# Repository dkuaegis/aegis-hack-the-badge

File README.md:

# Hack The Badge Ver.3

## Sponsored by

<p align="center">
  
  &nbsp;&nbsp;&nbsp;&nbsp;
  
</p>

해당 프로젝트는 EasyEDA로 제작되었고 EasyEDA 측의 제작 지원을 받았습니다. <br>
PCB 제작은 JLCPCB 측의 지원을 받았습니다.

## 프로젝트 소개

`Hack The Badge Ver.3`는 정보보안 동아리 Aegis가 MSG CTF 본선
부스에서 운영하는 체험형 하드웨어 해킹 프로젝트입니다. ESP32-S3를
기반으로 OLED, 버튼, LED, USB Serial, UART, challenge pad, 부저를
하나의 PCB 배지에 구성해, 행사 배지와 해킹 문제 도구로 함께 사용할
수 있도록 제작했습니다.

## 제작 목적

참가자가 일반적인 소프트웨어 CTF를 넘어 실제 PCB의 입출력 장치와
통신 인터페이스를 직접 살펴보며 하드웨어 보안을 체험하도록 하는 것이
목표입니다. 문제 풀이 결과가 화면, LED, 소리로 즉시 반영되는 상호작용을
통해 하드웨어 해킹을 처음 접하는 참가자도 쉽게 몰입할 수 있도록
구성했습니다.

## 체험 활동

참가자는 배지를 USB로 연결한 뒤 다음 활동을 진행합니다.

- Serial 터미널에서 문제를 확인하고 FLAG를 제출합니다.
- OLED와 버튼으로 문제, 힌트, 미니게임을 이용합니다.
- UART와 challenge pad를 분석해 숨겨진 하드웨어 문제를 해결합니다.
- OLED, LED, 부저를 통해 문제 진행 상태와 완료 결과를 확인합니다.

## 현재 제작 리비전

- 리비전: Hack The Badge Ver.3
- MCU: ESP32-S3-WROOM-1-N8R8
- 디스플레이: HS96L03W2C03 0.96 inch I2C OLED, PCBA 이후 수작업 납땜
- 사용자 I/O: USB Serial, 3.3 V UART, 버튼 3개, 상태 LED 5개
- Challenge I/O: 1 kOhm 직렬 저항으로 보호되는 `C0`, `C1`, `C2` GPIO pad
- 관리자/디버그: 복구와 bring-up을 위한 후면 staff test pad
- 오디오: MOSFET으로 구동하는 passive buzzer
- PCB 스타일: 검정 solder mask, 흰색 silkscreen, Aegis 방패 외형

## 저장소 구조

```text
assets/brand/                         Aegis, MSG CTF, EasyEDA, JLCPCB 로고
docs/rev3/                            설계, 제작, 스폰서 관련 문서
hardware/design/rev3/kicad/           KiCad 호환 회로도, PCB, 라이브러리
hardware/design/rev3/reference/       BOM 메모, 데이터시트, 전기적 설계 메모
hardware/releases/rev3/jlcpcb/upload/ JLCPCB 업로드용 Gerber, BOM, CPL
hardware/releases/rev3/easyeda-pro/   EasyEDA Pro 프로젝트 패키지와 체크리스트
hardware/releases/rev3/jlcpcb/        제작 파일, 조립 파일, preview, 검증 리포트
archive/                              이전 설계/제작 이력
tools/                                문서 생성 보조 스크립트
firmware/                             ESP32-S3 문제/UI/관리자 펌웨어
admin/                                Python BLE 브리지와 로컬 웹 대시보드
player-console/                       플레이어용 Web Serial 콘솔과 Docker 배포 구성
```

펌웨어 빌드, 문제 교체, Serial 명령과 무선 관리자 사용법은
[`firmware/README.md`](firmware/README.md)를 참고하세요.
브리지 설치, OS별 실행법과 운영 안내는
[`admin/README.md`](admin/README.md)를 참고하세요.
플레이어용 브라우저 USB 콘솔의 Docker 실행과 HTTPS 배포 안내는
[`player-console/README.md`](player-console/README.md)를 참고하세요.

## 펌웨어 빠른 시작

먼저 루트의 `.env.example`을 `.env`로 복사하고 `BADGE_ADMIN_KEY`와
`BADGE_FINAL_FLAG`를 비공개로 설정하세요. 펌웨어 빌드와 관리자 브리지가 같은
파일을 읽습니다. `.env`와 펌웨어 바이너리는 공개하거나 Git에 추가하지 마세요.

펌웨어 대상은 `ESP32-S3-WROOM-1-N8R8`이며 PlatformIO 환경 이름은
`esp32-s3-rev3`입니다. 데이터 통신이 가능한 USB-C 케이블로 배지를 연결한
뒤 저장소 루트에서 다음 명령을 실행합니다.

```bash
cd firmware
pio run
pio device list
pio run -t upload
pio device monitor
```

`pio run`은 첫 실행 시 ESP32 플랫폼, Arduino framework와 U8g2 의존성을
자동으로 내려받아 빌드합니다. Serial monitor 속도는 `platformio.ini`에
`115200`으로 설정되어 있습니다. 포트 자동 선택이 실패하면 OS에서 확인한
포트를 직접 지정합니다.

```bash
# Windows 예시
pio run -t upload --upload-port COM5
pio device monitor --port COM5

# macOS 예시
pio run -t upload --upload-port /dev/cu.usbmodemXXXX
pio device monitor --port /dev/cu.usbmodemXXXX

# Linux 예시
pio run -t upload --upload-port /dev/ttyACM0
pio device monitor --port /dev/ttyACM0
```

업로드 포트가 나타나지 않으면 USB 케이블이 충전 전용인지 먼저 확인하고,
`BOOT` 버튼을 누른 상태에서 `EN`을 눌렀다 놓은 뒤 `BOOT`를 놓아 ROM 다운로드
모드로 진입한 다음 다시 업로드합니다. 일반 업로드는 NVS를 지우지 않으므로
기존 풀이 상태와 관리자 페이지에서 편집한 문제는 유지됩니다.

PlatformIO 설치, 완전 초기화, BOOT 복구, 업로드 후 점검, 핀 매핑과 보안
주의사항은 [`firmware/README.md`](firmware/README.md)의 상세 절차를
참고하세요.

## 소프트웨어 구조

참가자 USB Serial과 관리자 BLE 셸은 각자의 입력 상태를 따로 유지합니다.
관리자 PC에서는 하나의 Python 프로세스가 BLE Central, HTTP API,
정적 대시보드를 모두 제공합니다. 인터넷과 공유기는 필요하지 않고,
브라우저는 관리자 PC의 `127.0.0.1` 주소로만 접속합니다.

| 코드 | 역할 |
| --- | --- |
| `firmware/src/main.cpp` | 메인 루프, OLED UI, 버튼·LED, USB/BLE 셸, 미니게임, challenge pad 처리 |
| `firmware/src/problems.h` | 1~4번 기본 문제, 문제 크기 제한, 미니게임 보상 문구 |
| `firmware/src/pins.h` | Rev.3 PCB의 GPIO 매핑 |
| `firmware/src/logic.h` | 상태 비트와 challenge pad 판정 로직 |
| `admin/bridge.py` | 배지 탐색·인증·연결, HTTP API, 대시보드 서빙 |
| `admin/dashboard/index.html` | 배지별 상태, 관리자 셸, 리셋·재부팅·문제 편집 UI |
| `admin/start.py` | 가상환경 생성, pip 의존성 확인·설치, 자가 검사, 서버 실행 |
| `player-console/` | 관리자 기능 없이 브라우저와 USB CDC를 직접 연결하는 정적 웹 콘솔 |

## 참가자 사용 설명서

1. 배지를 USB로 PC에 연결하고 Serial 터미널을 `115200 baud`로 엽니다.
2. `aegis`를 입력한 뒤 `1`~`4`로 문제를 선택합니다.
3. 한국어 문제 본문은 Serial에서, 영문 ASCII 힌트는 OLED에서 확인합니다.
4. 문제 안내에 따라 문제 내부 명령 또는 FLAG를 Serial에 입력합니다.
5. 해결한 문제는 상태 LED와 OLED `STATUS`에 반영됩니다.

Serial 명령:

| 명령 | 기능 |
| --- | --- |
| `1`~`4` | 문제 선택 |
| `hint` | 선택한 문제의 OLED 보기/예시 재표시 |
| `exit` | 현재 문제 나가기 |
| `status` | 문제 풀이 상태 표시 |
| `help` | 사용 가능한 명령 표시 |
| `clear` | Serial 터미널 화면 정리 |
| `aegis` | 시작 배너 재표시 |

OLED 하단의 `LEFT`, `OK`, `RIGHT` 버튼으로 메뉴 이동과 Flappy Hacker를
조작합니다. 미니게임에서 목표 점수를 넘기면 OLED에 추가 힌트가
표시됩니다.

## 관리자 사용 설명서

Python 3.10 이상과 Bluetooth LE가 가능한 PC에서 해당 OS의 스크립트를
실행합니다. 첫 실행 시 `admin/.venv`를 만들고 필요한 pip 패키지를
자동 설치한 뒤 브리지를 시작합니다. 운영 키는 환경변수 또는
`--admin-key '32바이트 이상의 키'`로 전달할 수 있으며, 공개 개발 키는
명령에 `--allow-dev-key`를 붙인 로컬 테스트에서만 허용됩니다.

```bash
# macOS
./admin/start-macos.sh --admin-key 'AEGIS_DEV_ONLY_CHANGE_ME'

# Linux
./admin/start-linux.sh --admin-key 'AEGIS_DEV_ONLY_CHANGE_ME'
```

Windows에서는 터미널에서 `admin\start-windows.bat`을 실행하거나 파일을
더블 클릭합니다. 시작 후 브라우저에서 `http://127.0.0.1:8080`을 엽니다.

대시보드에서 배지를 선택하면 다음 작업을 수행할 수 있습니다.

- 1~4번과 Hidden Access의 풀이 상태 확인
- 개별 또는 현재 연결된 전체 배지의 풀이 상태 초기화·재부팅
- USB 사용자 셸 기능을 포함한 BLE 관리자 셸 사용
- 1~4번 문제의 FLAG/최대 4지선다 유형 개별·일괄 수정

행사 전에는 펌웨어와 브리지의 `BADGE_ADMIN_KEY`를 동일한 운영용
키로 교체하세요. 자세한 OS별 준비, 설정, 문제 편집 제한과 문제 해결은
[`admin/README.md`](admin/README.md)에 정리했습니다.

## 제작 산출물

JLCPCB 업로드 파일:

| 단계     | 파일                                                                       |
| -------- | -------------------------------------------------------------------------- |
| PCB 제작 | `hardware/releases/rev3/jlcpcb/upload/hacking_badge_v3_jlcpcb_gerbers.zip` |
| PCBA BOM | `hardware/releases/rev3/jlcpcb/upload/hacking_badge_v3_jlcpcb_bom.csv`     |
| PCBA CPL | `hardware/releases/rev3/jlcpcb/upload/hacking_badge_v3_jlcpcb_cpl.csv`     |

EasyEDA Pro 프로젝트 패키지:

| 용도                             | 파일                                                                                            |
| -------------------------------- | ----------------------------------------------------------------------------------------------- |
| EasyEDA Pro 실크 호환 프로젝트   | `hardware/releases/rev3/easyeda-pro/upload/hacking_badge_v3_easyeda_pro_silk_compat_import.zip` |
| EasyEDA Pro 프로젝트(KiCad 호환) | `hardware/releases/rev3/easyeda-pro/upload/hacking_badge_v3_easyeda_pro_kicad_import.zip`       |
| EasyEDA Pro 프로젝트 아카이브    | `hardware/releases/rev3/easyeda-pro/reference/ProPrj_hack_the_badge_rev.3.epro2`                |

## 3D Preview

홍보물 제작이나 웹/Blender preview에는 검정 PCB 색상이 보정된 GLB 파일을
사용하는 것을 권장합니다.

| 용도                    | 파일                                                                                |
| ----------------------- | ----------------------------------------------------------------------------------- |
| 검정 PCB 홍보용 GLB     | `hardware/releases/rev3/jlcpcb/preview/3d/hacking_badge_v3_full_assembly_black.glb` |
| 검정 PCB 3D export 묶음 | `hardware/releases/rev3/jlcpcb/preview/3d/hacking_badge_v3_3d_exports_black.zip`    |
| 전체 3D export 묶음     | `hardware/releases/rev3/jlcpcb/preview/3d/hacking_badge_v3_3d_exports.zip`          |

## 검증 상태

현재 확인된 상태:

- Schematic ERC: 0 errors, 0 warnings
- Schematic-to-PCB validation: PASS
- JLCPCB manufacturing validation: PASS
- Gerber ZIP SHA256:
  `b55b42de45568e995e8cb47bb18cfc09abd5469c50e1fb60852d323a703e96b1`

유용한 검증 명령:

```bash
/Applications/KiCad/KiCad.app/Contents/MacOS/kicad-cli sch erc \
  --format report \
  -o hardware/design/rev3/kicad/reports/erc-final.rpt \
  hardware/design/rev3/kicad/hacking_box_v2.kicad_sch

/Applications/KiCad/KiCad.app/Contents/Frameworks/Python.framework/Versions/3.9/bin/python3.9 \
  hardware/design/rev3/kicad/scripts/validate_schematic_against_pcb.py

/Applications/KiCad/KiCad.app/Contents/Frameworks/Python.framework/Versions/3.9/bin/python3.9 \
  hardware/design/rev3/kicad/scripts/validate_manufacturing.py
```

## 참고 사항

- KiCad 파일명은 초기 프로젝트/라이브러리 이름을 유지하기 위해
  `hacking_box_v2`를 사용합니다. 실제 제작 리비전은 Ver.3입니다.
- `OLED1`은 JLCPCB BOM/CPL에서 제외되어 있으며, 별도 구매 후 수작업으로
  납땜하는 기준입니다.
- JLCPCB SMT viewer에서 자동 placement alignment 알림이 뜨면 취소하고,
  기존 CPL 기준 배치가 유지되는지 확인합니다. 방패 형태의 custom outline
  때문에 false offset warning이 뜰 수 있습니다.
- Challenge pad는 3.3 V GPIO 전용입니다. 회로를 의도적으로 수정하지 않은
  상태에서 `VBUS`, `3V3`, `EN`, `BOOT` 단락을 문제 풀이 요소로 노출하지
  마세요.

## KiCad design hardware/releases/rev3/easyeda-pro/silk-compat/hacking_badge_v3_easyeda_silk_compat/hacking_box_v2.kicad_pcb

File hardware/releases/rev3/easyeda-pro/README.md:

# Hacking Badge Ver.3 EasyEDA Pro Package

This directory contains the EasyEDA Pro preparation package for sponsor/coupon
workflow.

## Upload / Import Files

| Purpose | File |
| --- | --- |
| Recommended EasyEDA Pro import package | `upload/hacking_badge_v3_easyeda_pro_silk_compat_import.zip` |
| Raw KiCad source import package | `upload/hacking_badge_v3_easyeda_pro_kicad_import.zip` |
| Previous EasyEDA Pro archive reference | `reference/ProPrj_hack_the_badge_rev.3.epro2` |

Use the silkscreen-compatible import package first when the goal is sponsor
review or coupon use in EasyEDA Pro. It is derived from the current production
KiCad design, but converts filled silkscreen polygons into dense line artwork
because EasyEDA Pro's KiCad importer can otherwise show complex filled logos as
hollow outlines. The raw KiCad import package is kept only as a reference for
format comparison. The `.epro2` file is kept as a reference/native archive
candidate, but it was generated before the final KiCad release checks and must
not be assumed to be identical without review.

## Import Procedure

1. Open EasyEDA Pro.
2. Use the start page import flow for KiCad files, or use the EasyEDA Pro Format
   Converter if direct import fails.
3. Select `upload/hacking_badge_v3_easyeda_pro_silk_compat_import.zip`.
4. After import, open both schematic and PCB.
5. Rebuild/refill copper zones only if EasyEDA Pro asks for it, then compare
   against the KiCad release previews and Gerbers.
6. Run EasyEDA Pro DRC/ERC before using any generated manufacturing output.

## Required Post-Import Checks

- Board outline remains the Aegis shield shape, approximately 84.05 x 100.05 mm.
- USB-C connector sits on the bottom edge with the intentional edge overhang.
- ESP32-S3 antenna keep-out is still clear.
- Front silkscreen includes `Aegis X MSG CTF`, `HACK THE BADGE Ver.3`,
  `Developed By @Z3r0c0k3_`, full Aegis logo, and sponsor mark.
- Rear silkscreen preserves the filled Aegis silhouette and MSG CTF negative
  mark.
- Filled logo areas may look lightly striped at extreme zoom because the
  EasyEDA-compatible package uses dense silkscreen lines instead of KiCad
  filled polygons.
- `C0`, `C1`, `C2` challenge pads route through 1 kOhm series resistors to
  ESP32-S3 GPIO6, GPIO7, GPIO8.
- OLED pin order remains `GND, VCC, SCL, SDA`.
- J1, U1, U2, D1, Q_BZ, LEDs, buzzer diode, and switches have correct rotation.
- Copper zones and clearances match the KiCad/JLCPCB manufacturing release.

## Important Warning

The routed KiCad project and the JLCPCB release package remain the production
source of truth until the EasyEDA Pro import is manually reviewed. EasyEDA Pro
can import KiCad files, but format conversion can change copper-zone results.
Do not manufacture from newly generated EasyEDA Pro Gerbers until visual review,
DRC/ERC, and pin/net checks pass.

## Checksums

See `SHA256SUMS.txt`.

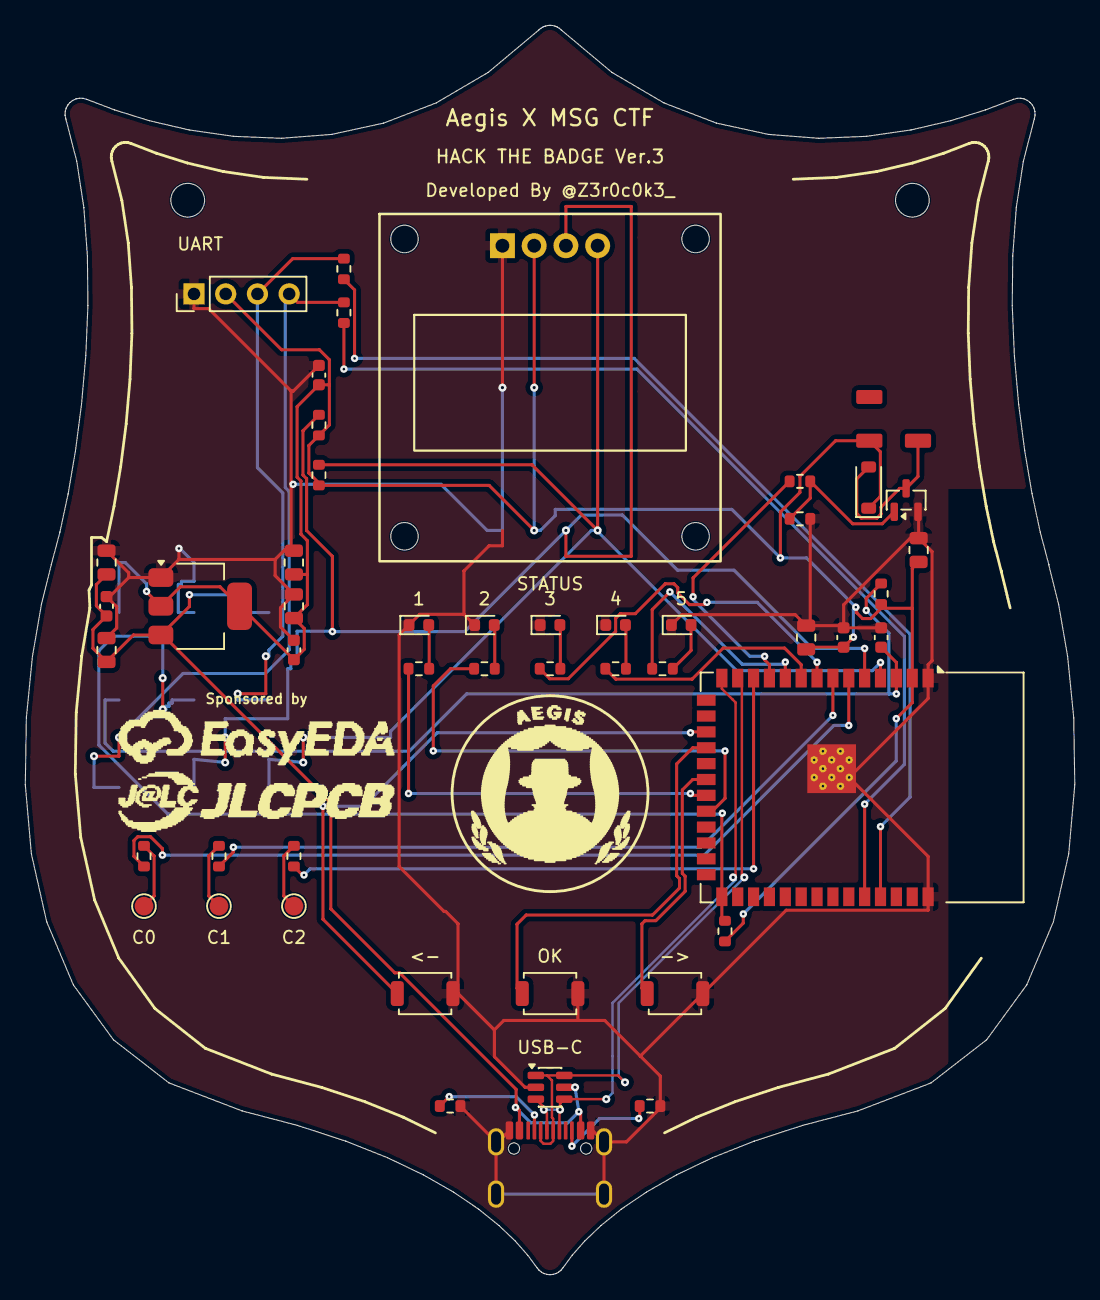
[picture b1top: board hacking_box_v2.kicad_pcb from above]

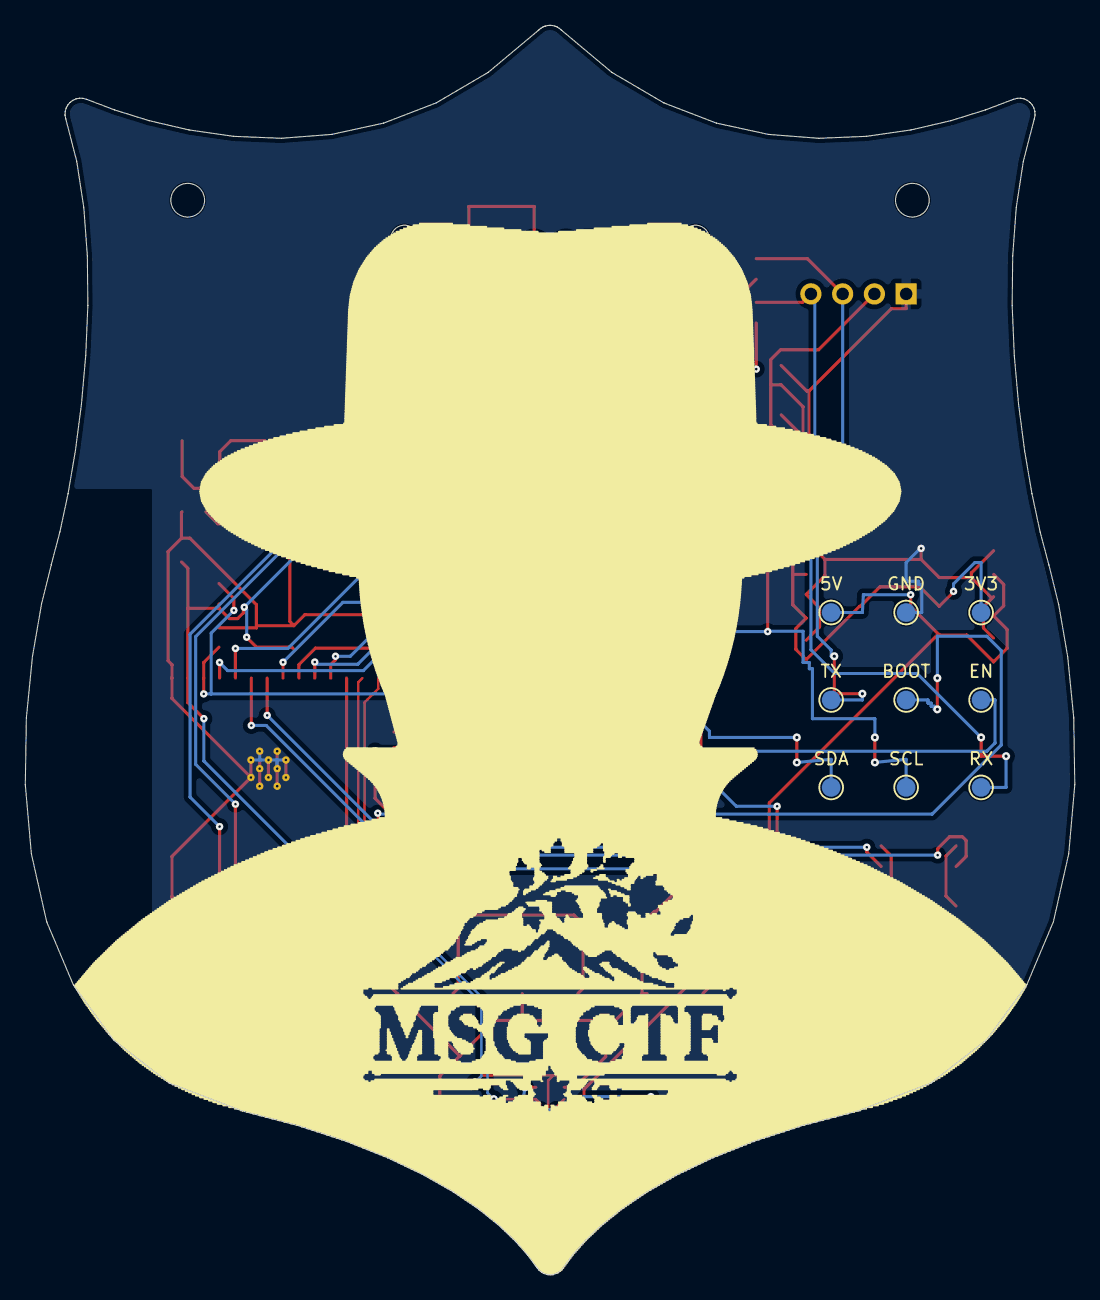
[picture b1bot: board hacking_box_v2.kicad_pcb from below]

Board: 2 copper layers, 84.0 x 100.0 mm, 60 parts (9 on the bottom side), 37 nets.

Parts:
BZ1: SMD5020-ZK; Buzzer_SMD5020_ZK
C1, C3, C4, C5, C7, C9: 10uF; C_0805_2012Metric
C2, C6, C8: 100nF; C_0603_1608Metric
C_EN: 1uF; C_0603_1608Metric
C_OLED: 100nF; C_0603_1608Metric
D1: USBLC6-2SC6; SOT-23-6
D_BZ: 1N4148W; D_SOD-123
H1, H2: LANYARD; MountingHole_2.7mm
J1: TYPE-C-31-M-12; USB_C_Receptacle_HRO_TYPE-C-31-M-12
LED1, LED2, LED3, LED4, LED5: RED_STATUS; LED_0603_1608Metric
OLED1: HS96L03W2C03; OLED_HS96L03W2C03
P_CHAL0, P_CHAL1, P_CHAL2: TP; TestPoint_Pad_D1.5mm
P_UART: UART_GND_3V3_TX_RX; PinHeader_1x04_P2.54mm_Vertical
Q_BZ: AO3400A; SOT-23
R1, R2: 5.1k; R_0603_1608Metric
R_BOOT: 10k; R_0603_1608Metric
R_BZ: 1k; R_0603_1608Metric
R_BZ_PD: 10k; R_0603_1608Metric
R_CHAL0, R_CHAL1, R_CHAL2: 1k; R_0603_1608Metric
R_EN: 10k; R_0603_1608Metric
R_LED1, R_LED2, R_LED3, R_LED4, R_LED5: 1k; R_0603_1608Metric
R_SCL: 10k; R_0603_1608Metric
R_SDA: 10k; R_0603_1608Metric
R_UART_RX: 1k; R_0603_1608Metric
R_UART_TX: 1k; R_0603_1608Metric
SW_ADMIN: ADMIN; SW_SPST_TS-1088-xR020
SW_BOOT: BOOT; SW_SPST_TS-1088-xR020
SW_EN: RESET; SW_SPST_TS-1088-xR020
TP_3V3: TP; TestPoint_Pad_D1.5mm
TP_BOOT: TP; TestPoint_Pad_D1.5mm
TP_EN: TP; TestPoint_Pad_D1.5mm
TP_GND: TP; TestPoint_Pad_D1.5mm
TP_OLED_SCL: TP; TestPoint_Pad_D1.5mm
TP_OLED_SDA: TP; TestPoint_Pad_D1.5mm
TP_UART_RX: TP; TestPoint_Pad_D1.5mm
TP_UART_TX: TP; TestPoint_Pad_D1.5mm
TP_VBUS: TP; TestPoint_Pad_D1.5mm
U1: ESP32-S3-WROOM-1-N8R8; ESP32-S3-WROOM-1
U2: AMS1117-3.3; SOT-223-3_TabPin2

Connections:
3V3: BZ1.1, C4.1, C5.1, C6.1, C7.1, C8.1, C9.1, C_OLED.1, D_BZ.1, OLED1.2, P_UART.2, R_BOOT.1, R_EN.1, R_SCL.1, R_SDA.1, TP_3V3.1, U1.2, U2.2
BOOT_GPIO0: R_BOOT.2, TP_BOOT.1, U1.27
BUZZER_GATE: Q_BZ.1, R_BZ.2, R_BZ_PD.1
BUZZER_GPIO: R_BZ.1, U1.11
BUZZER_SW: BZ1.2, D_BZ.2, Q_BZ.3
CHAL_0: P_CHAL0.1, R_CHAL0.2
CHAL_0_MCU: R_CHAL0.1, U1.6
CHAL_1: P_CHAL1.1, R_CHAL1.2
CHAL_1_MCU: R_CHAL1.1, U1.7
CHAL_2: P_CHAL2.1, R_CHAL2.2
CHAL_2_MCU: R_CHAL2.1, U1.12
EN: C_EN.1, R_EN.2, TP_EN.1, U1.3
GAME_LEFT: SW_EN.1, U1.17
GAME_OK: SW_BOOT.1, U1.18
GAME_RIGHT: SW_ADMIN.1, U1.20
GND: C1.2, C2.2, C3.2, C4.2, C5.2, C6.2, C7.2, C8.2, C9.2, C_EN.2, C_OLED.2, D1.2, J1.A1, J1.A12, J1.B1, J1.B12, J1.SH, LED1.1, LED2.1, LED3.1, LED4.1, LED5.1, OLED1.1, P_UART.1, Q_BZ.2, R1.2, R2.2, R_BZ_PD.2, SW_ADMIN.2, SW_BOOT.2, SW_EN.2, TP_GND.1, U1.1, U1.40, U1.41, U2.1
OLED_SCL: OLED1.3, R_SCL.2, TP_OLED_SCL.1, U1.5
OLED_SDA: OLED1.4, R_SDA.2, TP_OLED_SDA.1, U1.4
PLAYER_UART_RX: P_UART.4, R_UART_RX.2, TP_UART_RX.1
PLAYER_UART_TX: P_UART.3, R_UART_TX.2, TP_UART_TX.1
STATUS_LED_1_A: LED1.2, R_LED1.2
STATUS_LED_1_MCU: R_LED1.1, U1.21
STATUS_LED_2_A: LED2.2, R_LED2.2
STATUS_LED_2_MCU: R_LED2.1, U1.22
STATUS_LED_3_A: LED3.2, R_LED3.2
STATUS_LED_3_MCU: R_LED3.1, U1.8
STATUS_LED_4_A: LED4.2, R_LED4.2
STATUS_LED_4_MCU: R_LED4.1, U1.9
STATUS_LED_5_A: LED5.2, R_LED5.2
STATUS_LED_5_MCU: R_LED5.1, U1.10
UART_RX_MCU: R_UART_RX.1, U1.36
UART_TX_MCU: R_UART_TX.1, U1.37
USB_CC1: J1.A5, R1.1
USB_CC2: J1.B5, R2.1
USB_D_N: D1.1, D1.6, J1.A7, J1.B7, U1.13
USB_D_P: D1.3, D1.4, J1.A6, J1.B6, U1.14
VBUS: C1.1, C2.1, C3.1, D1.5, J1.A4, J1.A9, J1.B4, J1.B9, TP_VBUS.1, U2.3
